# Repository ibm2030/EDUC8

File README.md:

# EDUC8
EDUC-8 recreation by Gwyllym Suter
NOTE: 2024-04-01 PCBs are in the process of being updated and so do not match the latest schematics

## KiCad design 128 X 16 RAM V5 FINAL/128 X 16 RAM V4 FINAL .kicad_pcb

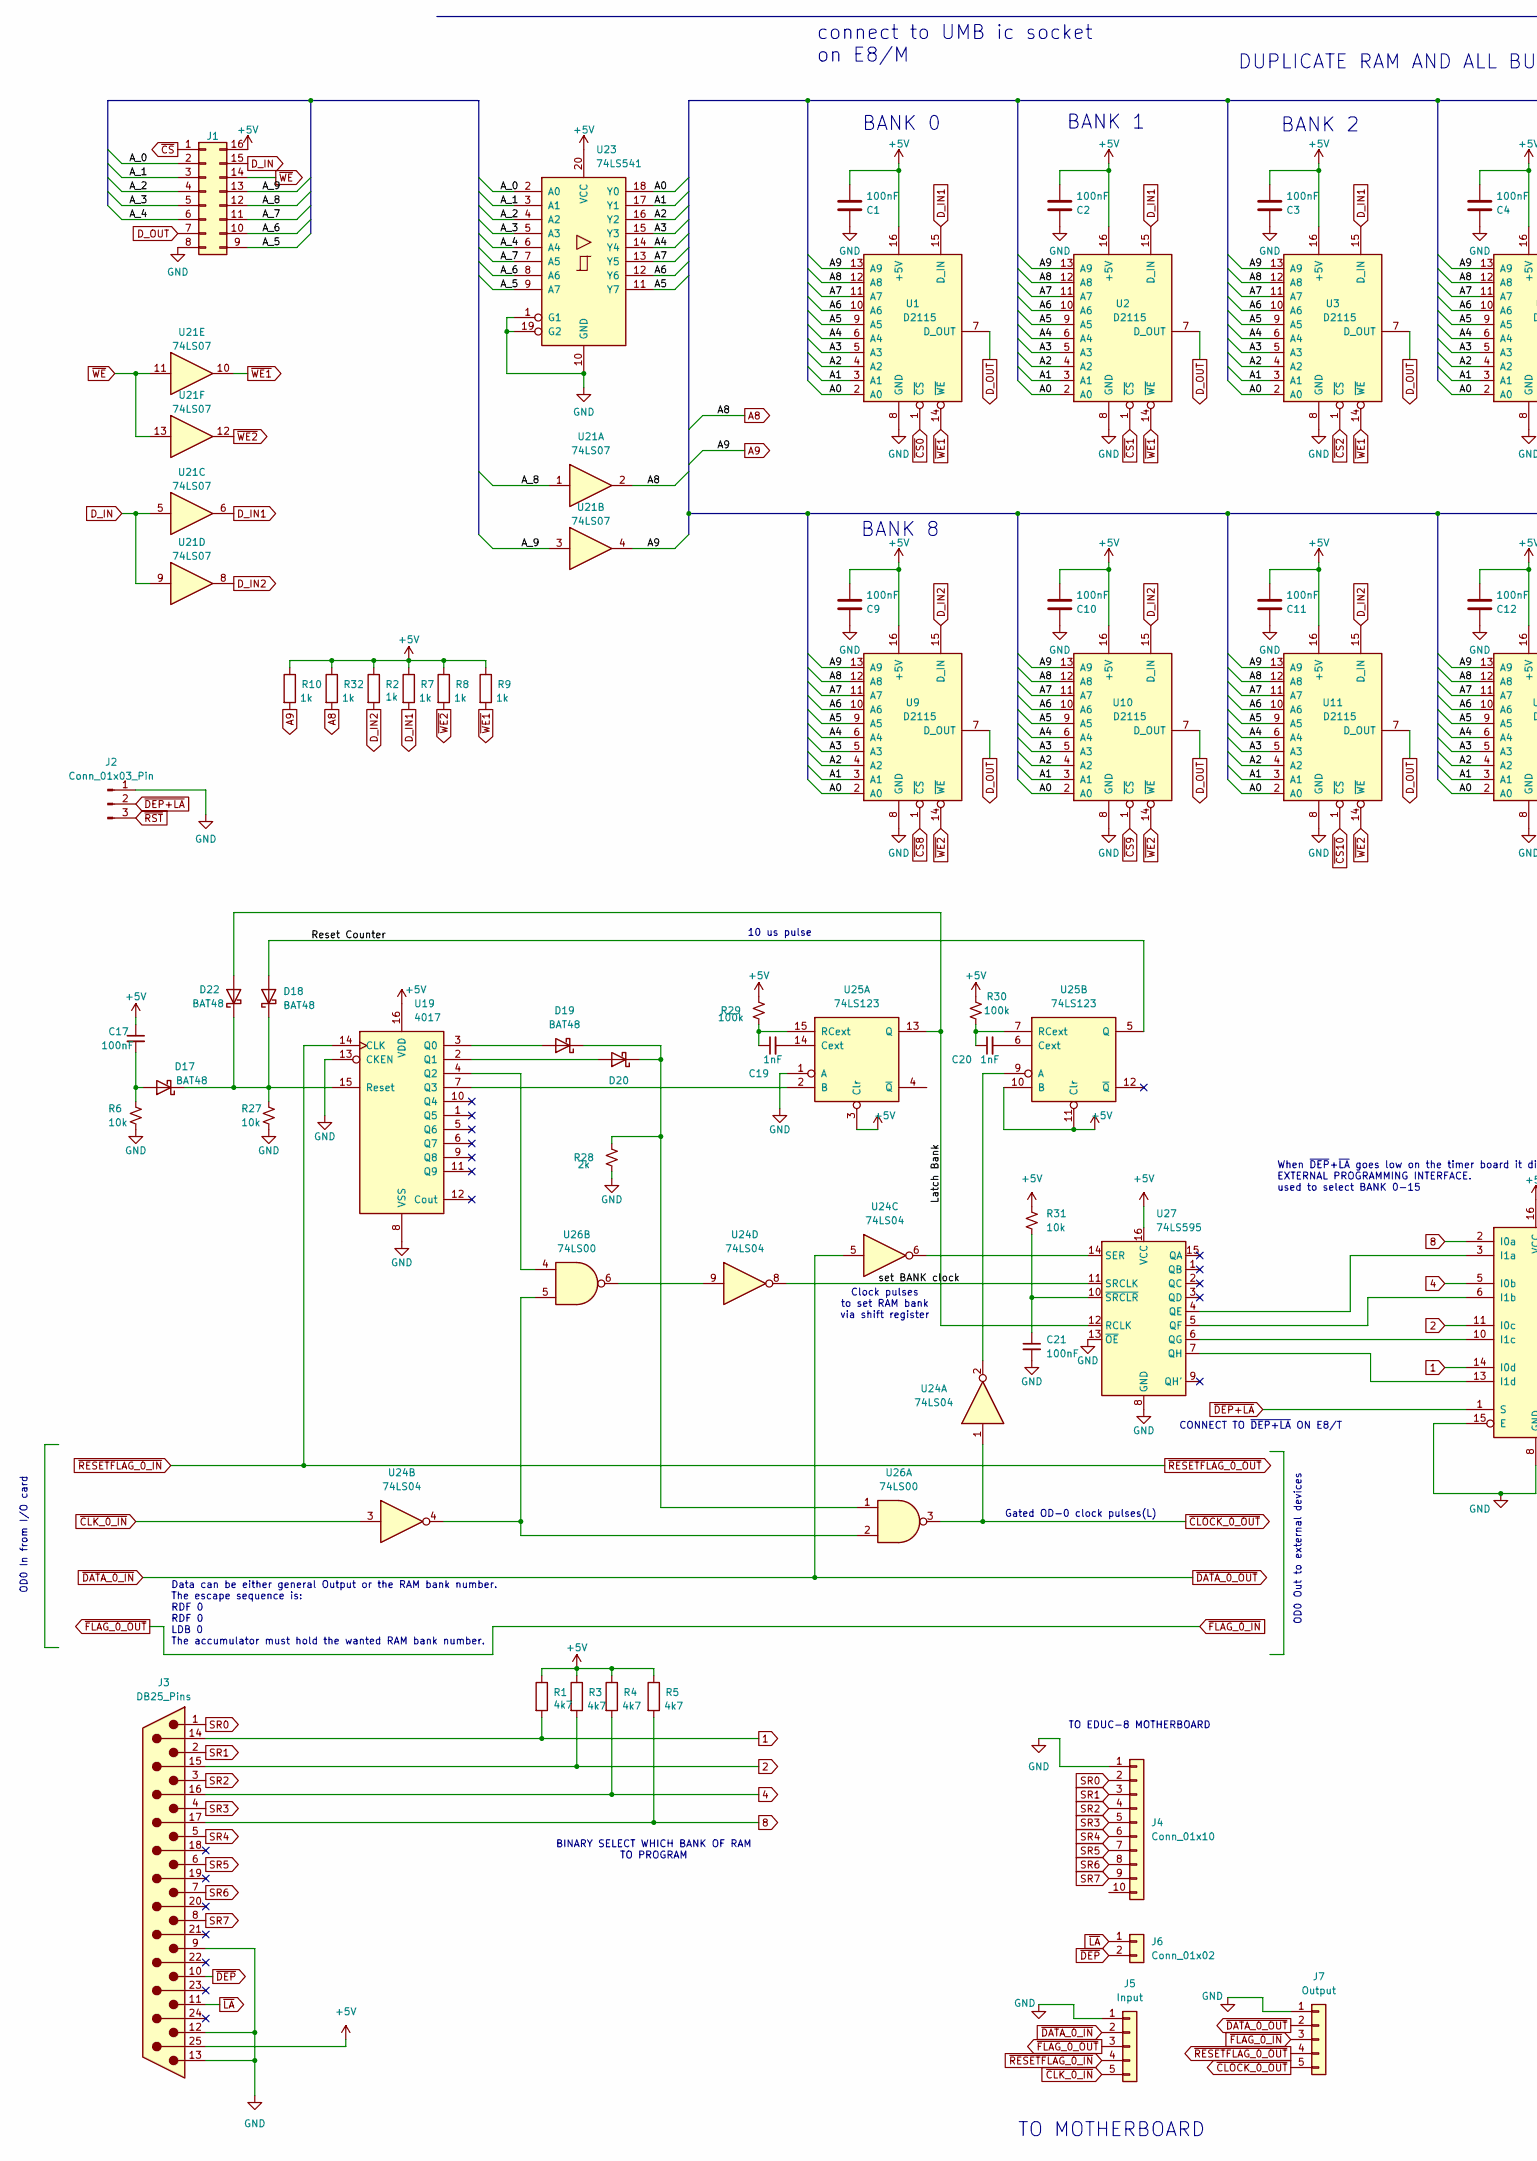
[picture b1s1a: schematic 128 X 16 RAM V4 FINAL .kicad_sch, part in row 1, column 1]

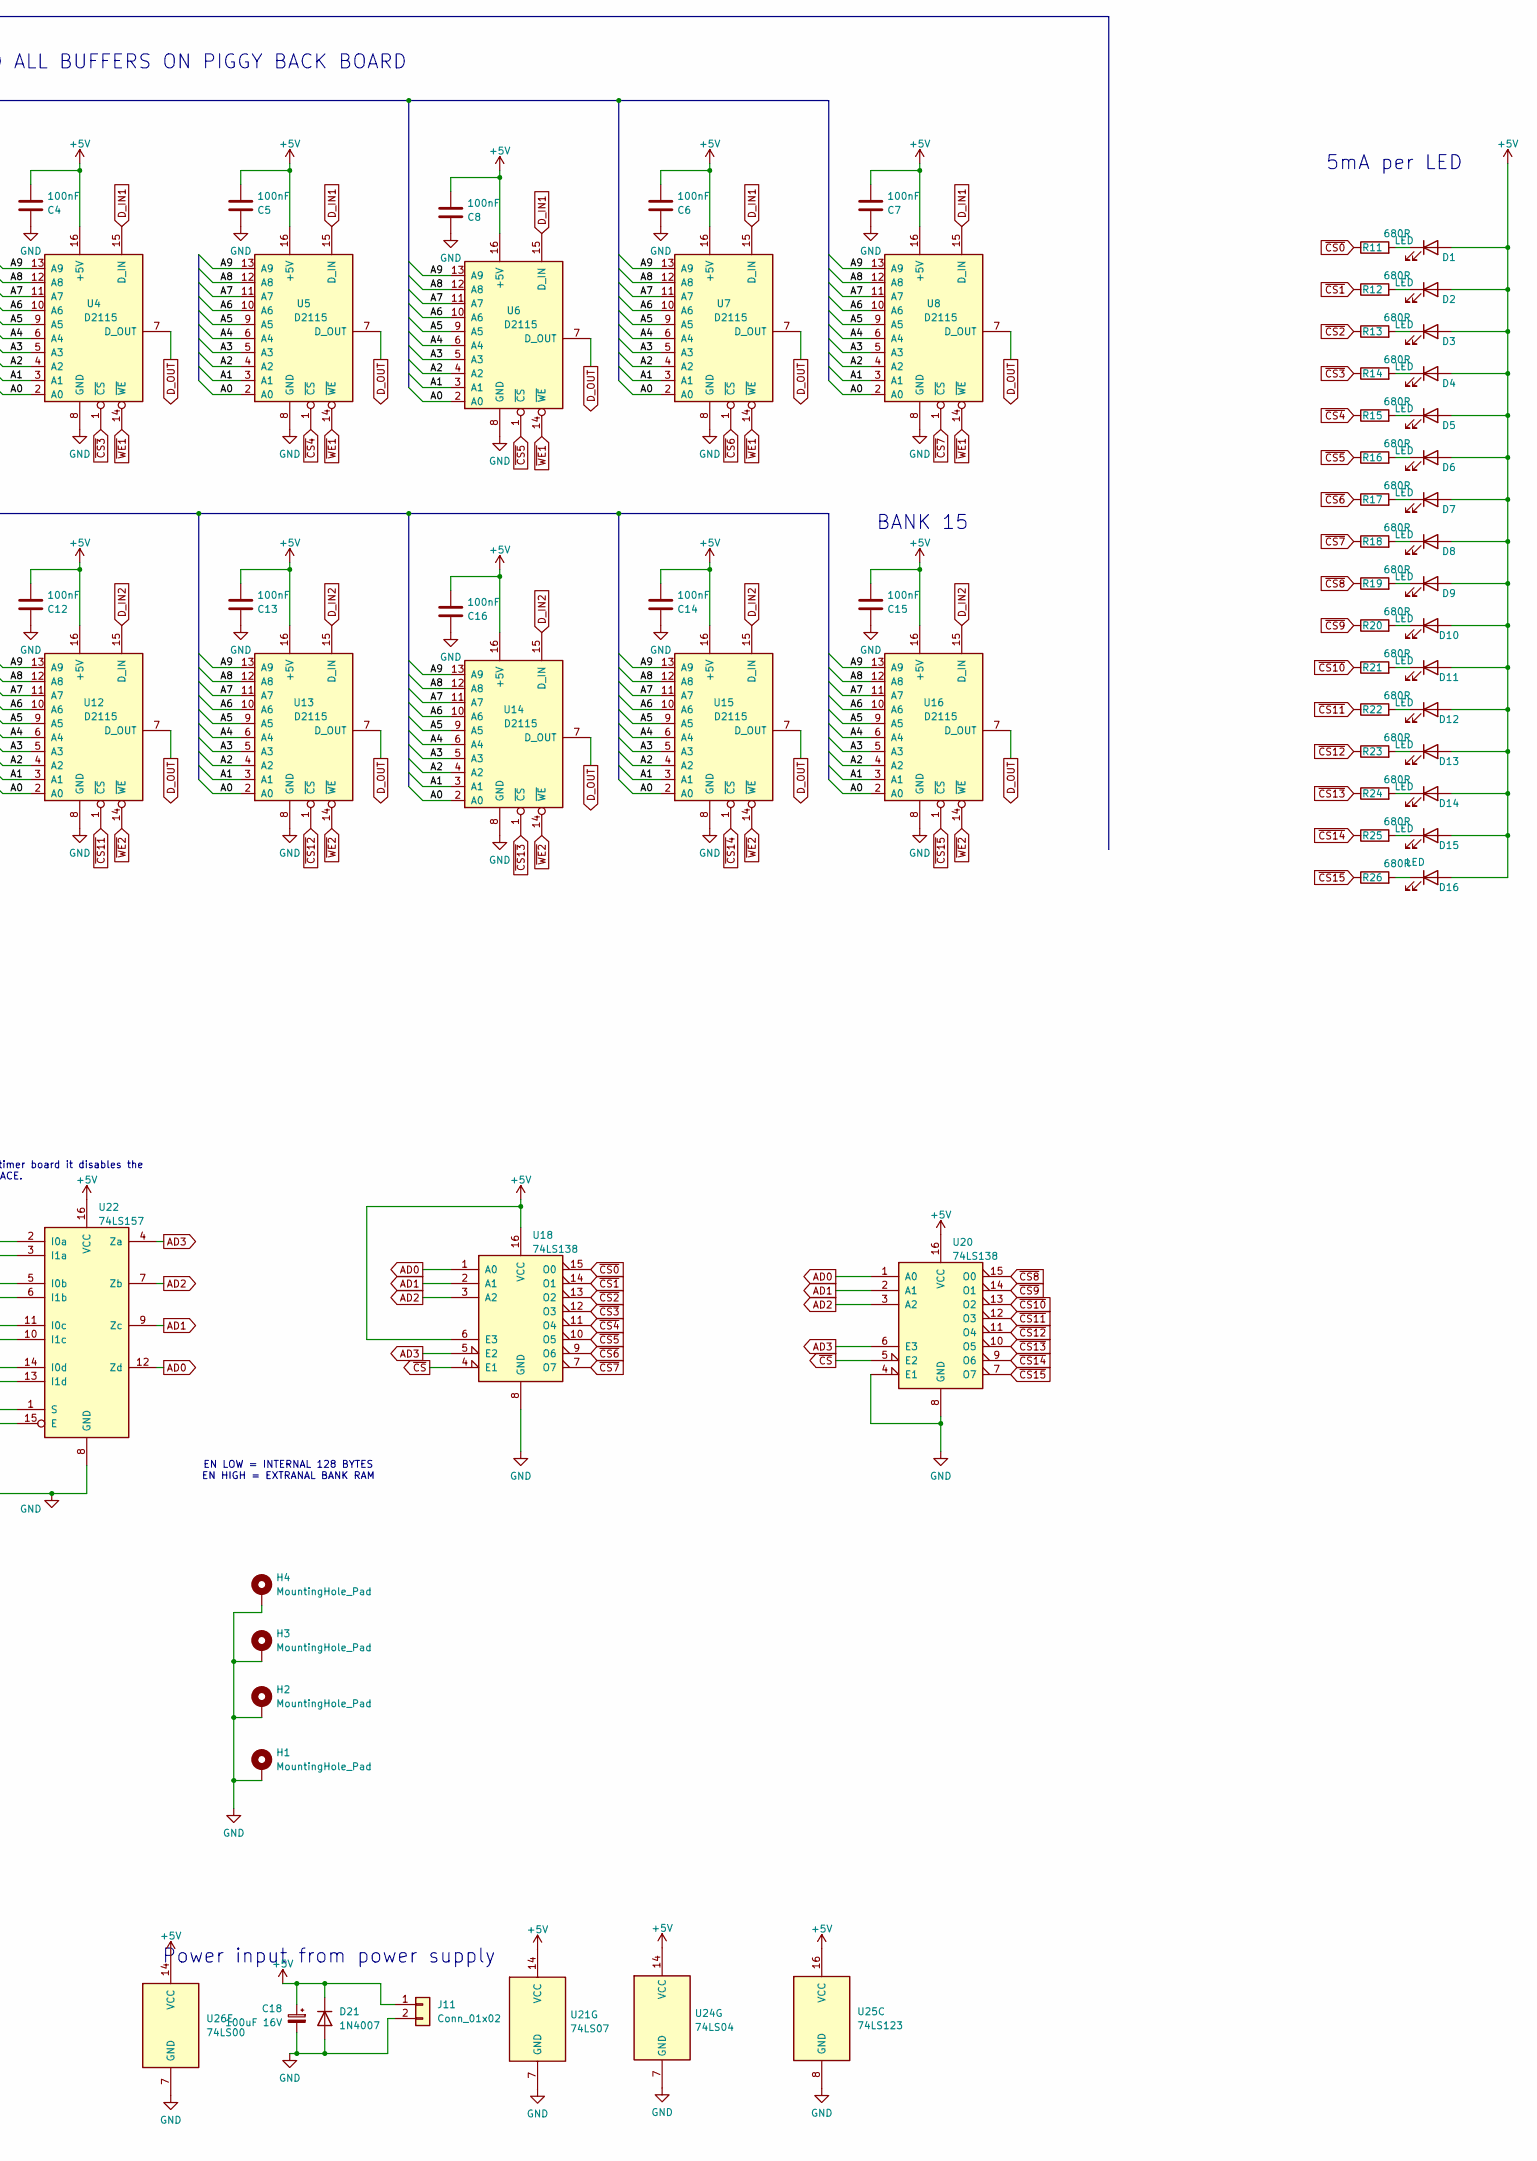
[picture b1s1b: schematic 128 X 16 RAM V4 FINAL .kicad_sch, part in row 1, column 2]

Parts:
C1, C2, C3, C4, C5, C6, C7, C8, C9, C10, C11, C12, C13, C14, C15, C16, C17, C21: 100nF; C_Disc_D4.3mm_W1.9mm_P5.00mm
C18: 100uF 16V; CP_Radial_D12.5mm_P5.00mm
C19, C20: 1nF; C_Disc_D4.3mm_W1.9mm_P5.00mm
D1, D2, D3, D4, D5, D6, D7, D8, D9, D10, D11, D12, D13, D14, D15, D16: LED; LED_D3.0mm
D17, D18, D19, D20, D22: BAT48; D_DO-35_SOD27_P7.62mm_Horizontal
D21: 1N4007; D_DO-41_SOD81_P10.16mm_Horizontal
H1, H2, H3, H4: MountingHole_Pad; MountingHole_3.2mm_M3_DIN965_Pad
J1: Conn_02x08_Counter_Clockwise; DIP-16_W7.62mm_Socket_LongPads
J2: Conn_01x03_Pin; JST_XH_B3B-XH-A_1x03_P2.50mm_Vertical
J3: DB25_Pins; DSUB-25_Pins_Horizontal_P2.77x2.84mm_EdgePinOffset7.70mm_Ho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
J4: Conn_01x10; JST_XH_B10B-XH-A_1x10_P2.50mm_Vertical
J5: Input; JST_XH_B5B-XH-A_1x05_P2.50mm_Vertical
J6: Conn_01x02; JST_XH_B2B-XH-A_1x02_P2.50mm_Vertical
J7: Output; JST_XH_B5B-XH-A_1x05_P2.50mm_Vertical
J11: Conn_01x02; TerminalBlock_Phoenix_MKDS-1,5-2-5.08_1x02_P5.08mm_Horizont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
R1, R3, R4, R5: 4k7; R_Axial_DIN0207_L6.3mm_D2.5mm_P10.16mm_Horizontal
R2, R7, R8, R9, R10, R32: 1k; R_Axial_DIN0207_L6.3mm_D2.5mm_P10.16mm_Horizontal
R6, R27, R31: 10k; R_Axial_DIN0207_L6.3mm_D2.5mm_P10.16mm_Horizontal
R11, R12, R13, R14, R15, R16, R17, R18, R19, R20, R21, R22, R23, R24, R25, R26: 680R; R_Axial_DIN0207_L6.3mm_D2.5mm_P10.16mm_Horizontal
R28: 2k; R_Axial_DIN0207_L6.3mm_D2.5mm_P10.16mm_Horizontal
R29, R30: 100k; R_Axial_DIN0207_L6.3mm_D2.5mm_P10.16mm_Horizontal
U1, U2, U3, U4, U5, U6, U7, U8, U9, U10, U11, U12, U13, U14, U15, U16: D2115; DIP-16_W7.62mm_LongPads
U18, U20: 74LS138; DIP-16_W7.62mm_LongPads
U19: 4017; DIP-16_W7.62mm_LongPads
U21: 74LS07; DIP-14_W7.62mm_LongPads
U22: 74LS157; DIP-16_W7.62mm_LongPads
U23: 74LS541; DIP-20_W7.62mm_LongPads
U24: 74LS04; DIP-14_W7.62mm_LongPads
U25: 74LS123; DIP-16_W7.62mm_LongPads
U26: 74LS00; DIP-14_W7.62mm_LongPads
U27: 74LS595; DIP-16_W7.62mm

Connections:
1: J3.14, R1.2, U22.14 (I0d)
2: J3.15, R3.2, U22.11 (I0c)
4: J3.16, R4.2, U22.5 (I0b)
8: J3.17, R5.2, U22.2 (I0a)
+5V: C1.2, C2.2, C3.2, C4.2, C5.2, C6.2, C7.2, C8.2, C9.2, C10.2, C11.2, C12.2, C13.2, C14.2, C15.2, C16.2, C17.1, C18.1, D1.2 (A), D2.2 (A), D3.2 (A), D4.2 (A), D5.2 (A), D6.2 (A), D7.2 (A), D8.2 (A), D9.2 (A), D10.2 (A), D11.2 (A), D12.2 (A), D13.2 (A), D14.2 (A), D15.2 (A), D16.2 (A), D21.1 (K), J1.16, J3.25, J11.1, R1.1, R2.1, R3.1, R4.1, R5.1, R7.1, R8.1, R9.1, R10.1, R29.1, R30.1, R31.1, R32.1, U1.16 (+5V), U2.16 (+5V), U3.16 (+5V), U4.16 (+5V), U5.16 (+5V), U6.16 (+5V), U7.16 (+5V), U8.16 (+5V), U9.16 (+5V), U10.16 (+5V), U11.16 (+5V), U12.16 (+5V), U13.16 (+5V), U14.16 (+5V), U15.16 (+5V), U16.16 (+5V), U18.6 (E3), U18.16 (VCC), U19.16 (VDD), U20.16 (VCC), U21.14 (VCC), U22.16 (VCC), U23.20 (VCC), U24.14 (VCC), U25.3 (Clr), U25.10 (B), U25.11 (Clr), U25.16 (VCC), U26.14 (VCC), U27.16 (VCC)
/A0: U1.2 (A0), U2.2 (A0), U3.2 (A0), U4.2 (A0), U5.2 (A0), U6.2 (A0), U7.2 (A0), U8.2 (A0), U9.2 (A0), U10.2 (A0), U11.2 (A0), U12.2 (A0), U13.2 (A0), U14.2 (A0), U15.2 (A0), U16.2 (A0), U23.18 (Y0)
/A1: U1.3 (A1), U2.3 (A1), U3.3 (A1), U4.3 (A1), U5.3 (A1), U6.3 (A1), U7.3 (A1), U8.3 (A1), U9.3 (A1), U10.3 (A1), U11.3 (A1), U12.3 (A1), U13.3 (A1), U14.3 (A1), U15.3 (A1), U16.3 (A1), U23.17 (Y1)
/A2: U1.4 (A2), U2.4 (A2), U3.4 (A2), U4.4 (A2), U5.4 (A2), U6.4 (A2), U7.4 (A2), U8.4 (A2), U9.4 (A2), U10.4 (A2), U11.4 (A2), U12.4 (A2), U13.4 (A2), U14.4 (A2), U15.4 (A2), U16.4 (A2), U23.16 (Y2)
/A3: U1.5 (A3), U2.5 (A3), U3.5 (A3), U4.5 (A3), U5.5 (A3), U6.5 (A3), U7.5 (A3), U8.5 (A3), U9.5 (A3), U10.5 (A3), U11.5 (A3), U12.5 (A3), U13.5 (A3), U14.5 (A3), U15.5 (A3), U16.5 (A3), U23.15 (Y3)
/A4: U1.6 (A4), U2.6 (A4), U3.6 (A4), U4.6 (A4), U5.6 (A4), U6.6 (A4), U7.6 (A4), U8.6 (A4), U9.6 (A4), U10.6 (A4), U11.6 (A4), U12.6 (A4), U13.6 (A4), U14.6 (A4), U15.6 (A4), U16.6 (A4), U23.14 (Y4)
/A5: U1.9 (A5), U2.9 (A5), U3.9 (A5), U4.9 (A5), U5.9 (A5), U6.9 (A5), U7.9 (A5), U8.9 (A5), U9.9 (A5), U10.9 (A5), U11.9 (A5), U12.9 (A5), U13.9 (A5), U14.9 (A5), U15.9 (A5), U16.9 (A5), U23.11 (Y7)
/A6: U1.10 (A6), U2.10 (A6), U3.10 (A6), U4.10 (A6), U5.10 (A6), U6.10 (A6), U7.10 (A6), U8.10 (A6), U9.10 (A6), U10.10 (A6), U11.10 (A6), U12.10 (A6), U13.10 (A6), U14.10 (A6), U15.10 (A6), U16.10 (A6), U23.12 (Y6)
/A7: U1.11 (A7), U2.11 (A7), U3.11 (A7), U4.11 (A7), U5.11 (A7), U6.11 (A7), U7.11 (A7), U8.11 (A7), U9.11 (A7), U10.11 (A7), U11.11 (A7), U12.11 (A7), U13.11 (A7), U14.11 (A7), U15.11 (A7), U16.11 (A7), U23.13 (Y5)
/A_0: J1.2, U23.2 (A0)
/A_1: J1.3, U23.3 (A1)
/A_2: J1.4, U23.4 (A2)
/A_3: J1.5, U23.5 (A3)
/A_4: J1.6, U23.6 (A4)
/A_5: J1.9, U23.9 (A7)
/A_6: J1.10, U23.8 (A6)
/A_7: J1.11, U23.7 (A5)
/A_8: J1.12, U21.1
/A_9: J1.13, U21.3
/Latch Bank: D22.2 (A), U25.13 (Q), U27.12 (RCLK)
/Reset Counter: D18.2 (A), U25.5 (Q)
/set BANK clock: U24.8, U27.11 (SRCLK)
A8: R32.2, U1.12 (A8), U2.12 (A8), U3.12 (A8), U4.12 (A8), U5.12 (A8), U6.12 (A8), U7.12 (A8), U8.12 (A8), U9.12 (A8), U10.12 (A8), U11.12 (A8), U12.12 (A8), U13.12 (A8), U14.12 (A8), U15.12 (A8), U16.12 (A8), U21.2
A9: R10.2, U1.13 (A9), U2.13 (A9), U3.13 (A9), U4.13 (A9), U5.13 (A9), U6.13 (A9), U7.13 (A9), U8.13 (A9), U9.13 (A9), U10.13 (A9), U11.13 (A9), U12.13 (A9), U13.13 (A9), U14.13 (A9), U15.13 (A9), U16.13 (A9), U21.4
AD0: U18.1 (A0), U20.1 (A0), U22.12 (Zd)
AD1: U18.2 (A1), U20.2 (A1), U22.9 (Zc)
AD2: U18.3 (A2), U20.3 (A2), U22.7 (Zb)
AD3: U18.5 (E2), U20.6 (E3), U22.4 (Za)
D_IN: J1.15, U21.5, U21.9
D_IN1: R7.2, U1.15 (D_IN), U2.15 (D_IN), U3.15 (D_IN), U4.15 (D_IN), U5.15 (D_IN), U6.15 (D_IN), U7.15 (D_IN), U8.15 (D_IN), U21.6
D_IN2: R2.2, U9.15 (D_IN), U10.15 (D_IN), U11.15 (D_IN), U12.15 (D_IN), U13.15 (D_IN), U14.15 (D_IN), U15.15 (D_IN), U16.15 (D_IN), U21.8
D_OUT: J1.7, U1.7 (D_OUT), U2.7 (D_OUT), U3.7 (D_OUT), U4.7 (D_OUT), U5.7 (D_OUT), U6.7 (D_OUT), U7.7 (D_OUT), U8.7 (D_OUT), U9.7 (D_OUT), U10.7 (D_OUT), U11.7 (D_OUT), U12.7 (D_OUT), U13.7 (D_OUT), U14.7 (D_OUT), U15.7 (D_OUT), U16.7 (D_OUT)
GND: C1.1, C2.1, C3.1, C4.1, C5.1, C6.1, C7.1, C8.1, C9.1, C10.1, C11.1, C12.1, C13.1, C14.1, C15.1, C16.1, C18.2, C21.2, D21.2 (A), H1.1, H2.1, H3.1, H4.1, J1.8, J2.1, J3.9, J3.12, J3.13, J4.1, J5.1, J7.1, J11.2, R6.2, R27.2, R28.2, U1.8 (GND), U2.8 (GND), U3.8 (GND), U4.8 (GND), U5.8 (GND), U6.8 (GND), U7.8 (GND), U8.8 (GND), U9.8 (GND), U10.8 (GND), U11.8 (GND), U12.8 (GND), U13.8 (GND), U14.8 (GND), U15.8 (GND), U16.8 (GND), U18.8 (GND), U19.8 (VSS), U19.13 (CKEN), U20.4 (E1), U20.8 (GND), U21.7 (GND), U22.8 (GND), U22.15 (E), U23.1 (G1), U23.10 (GND), U23.19 (G2), U24.7 (GND), U25.1 (A), U25.8 (GND), U26.7 (GND), U27.8 (GND), U27.13 (~OE)
unnamed: D1.1 (K), R11.2
unnamed: D2.1 (K), R12.2
unnamed: D3.1 (K), R13.2
unnamed: D4.1 (K), R14.2
unnamed: D5.1 (K), R15.2
unnamed: D6.1 (K), R16.2
unnamed: D7.1 (K), R17.2
unnamed: D8.1 (K), R18.2
unnamed: D9.1 (K), R19.2
unnamed: D10.1 (K), R20.2
unnamed: D11.1 (K), R21.2
unnamed: D12.1 (K), R22.2
unnamed: D13.1 (K), R23.2
unnamed: D14.1 (K), R24.2
unnamed: D15.1 (K), R25.2
unnamed: D16.1 (K), R26.2
unnamed: C17.2, D17.2 (A), R6.1
unnamed: D17.1 (K), D18.1 (K), D22.1 (K), R27.1, U19.15 (Reset)
unnamed: D19.2 (A), U19.3 (Q0)
unnamed: D19.1 (K), D20.1 (K), R28.1, U26.1
unnamed: D20.2 (A), U19.2 (Q1)
unnamed: U19.4 (Q2), U26.4
unnamed: U19.7 (Q3), U25.2 (B)
unnamed: U22.3 (I1a), U27.4 (QE)
unnamed: U22.6 (I1b), U27.5 (QF)
unnamed: U22.10 (I1c), U27.6 (QG)
unnamed: U22.13 (I1d), U27.7 (QH)
unnamed: U24.4, U26.2, U26.5
unnamed: U24.9, U26.6
unnamed: C19.2, U25.14 (Cext)
unnamed: C19.1, R29.2, U25.15 (RCext)
unnamed: U24.2, U25.9 (A)
unnamed: C20.2, U25.6 (Cext)
unnamed: C20.1, R30.2, U25.7 (RCext)
unnamed: U24.6, U27.14 (SER)
unnamed: C21.1, R31.2, U27.10 (~SRCLR)
SR0: J3.1, J4.2
SR1: J3.2, J4.3
SR2: J3.3, J4.4
SR3: J3.4, J4.5
SR4: J3.5, J4.6
SR5: J3.6, J4.7
SR6: J3.7, J4.8
SR7: J3.8, J4.9
~CLK_0_IN: J5.5, U24.3
~CLOCK_0_OUT: J7.5, U24.1, U26.3
~CS0: R11.1, U1.1 (~CS), U18.15 (O0)
~CS1: R12.1, U2.1 (~CS), U18.14 (O1)
~CS2: R13.1, U3.1 (~CS), U18.13 (O2)
~CS3: R14.1, U4.1 (~CS), U18.12 (O3)
~CS4: R15.1, U5.1 (~CS), U18.11 (O4)
~CS5: R16.1, U6.1 (~CS), U18.10 (O5)
~CS6: R17.1, U7.1 (~CS), U18.9 (O6)
~CS7: R18.1, U8.1 (~CS), U18.7 (O7)
~CS8: R19.1, U9.1 (~CS), U20.15 (O0)
~CS9: R20.1, U10.1 (~CS), U20.14 (O1)
~CS10: R21.1, U11.1 (~CS), U20.13 (O2)
~CS11: R22.1, U12.1 (~CS), U20.12 (O3)
~CS12: R23.1, U13.1 (~CS), U20.11 (O4)
~CS13: R24.1, U14.1 (~CS), U20.10 (O5)
~CS14: R25.1, U15.1 (~CS), U20.9 (O6)
~CS15: R26.1, U16.1 (~CS), U20.7 (O7)
~CS: J1.1, U18.4 (E1), U20.5 (E2)
~DATA_0_IN: J5.2, J7.2, U24.5
~DEP+LA: J2.2, U22.1 (S)
~DEP: J3.10, J6.2
~FLAG_0_IN: J5.3, J7.3
~LA: J3.11, J6.1
~RESETFLAG_0_IN: J5.4, J7.4, U19.14 (CLK)
~RST: J2.3
~WE1: R9.2, U1.14 (~WE), U2.14 (~WE), U3.14 (~WE), U4.14 (~WE), U5.14 (~WE), U6.14 (~WE), U7.14 (~WE), U8.14 (~WE), U21.10
~WE2: R8.2, U9.14 (~WE), U10.14 (~WE), U11.14 (~WE), U12.14 (~WE), U13.14 (~WE), U14.14 (~WE), U15.14 (~WE), U16.14 (~WE), U21.12
~WE: J1.14, U21.11, U21.13

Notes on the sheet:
connect to UMB ic socket on E8/M
10 us pulse
BANK 15
EN LOW = INTERNAL 128 BYTES EN HIGH = EXTRANAL BANK RAM
BANK 0
DUPLICATE RAM AND ALL BUFFERS ON PIGGY BACK BOARD
Gated OD-0 clock pulses(L)
TO EDUC-8 MOTHERBOARD
OD0 Out to external devices
When ~{DEP}+~{LA} goes low on the timer board it disables the EXTERNAL PROGRAMMING INTERFACE. used to select BANK 0-15
OD0 In from I/O card
Clock pulses to set RAM bank via shift register
Power input from power supply
BANK 8
5mA per LED
Data can be either general Output or the RAM bank number. The escape sequence is: RDF 0 RDF 0 LDB 0 The accumulator must hold the wanted RAM bank number.
BANK 1
BANK 2
CONNECT TO ~{DEP+LA} ON E8/T
TO MOTHERBOARD
BINARY SELECT WHICH BANK OF RAM TO PROGRAM

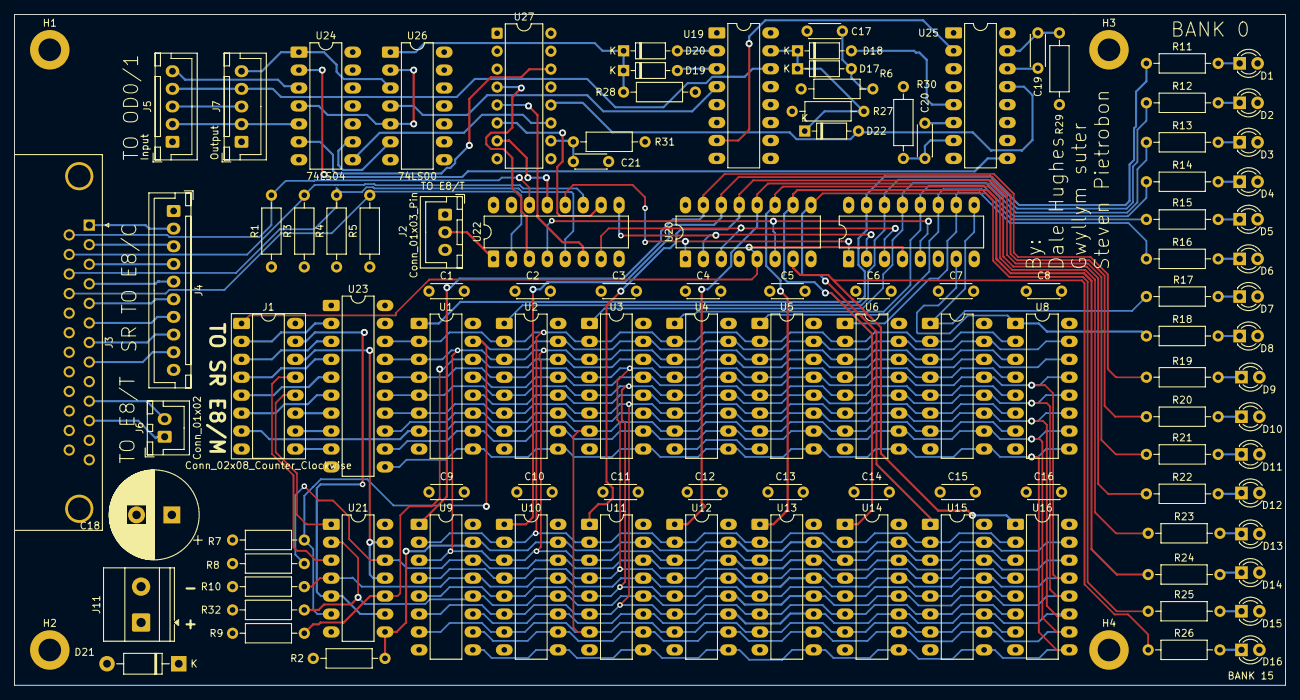
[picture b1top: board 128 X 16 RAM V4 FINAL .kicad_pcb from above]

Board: 4 copper layers, 180.0 x 95.0 mm, 113 parts (0 on the bottom side), 109 nets.

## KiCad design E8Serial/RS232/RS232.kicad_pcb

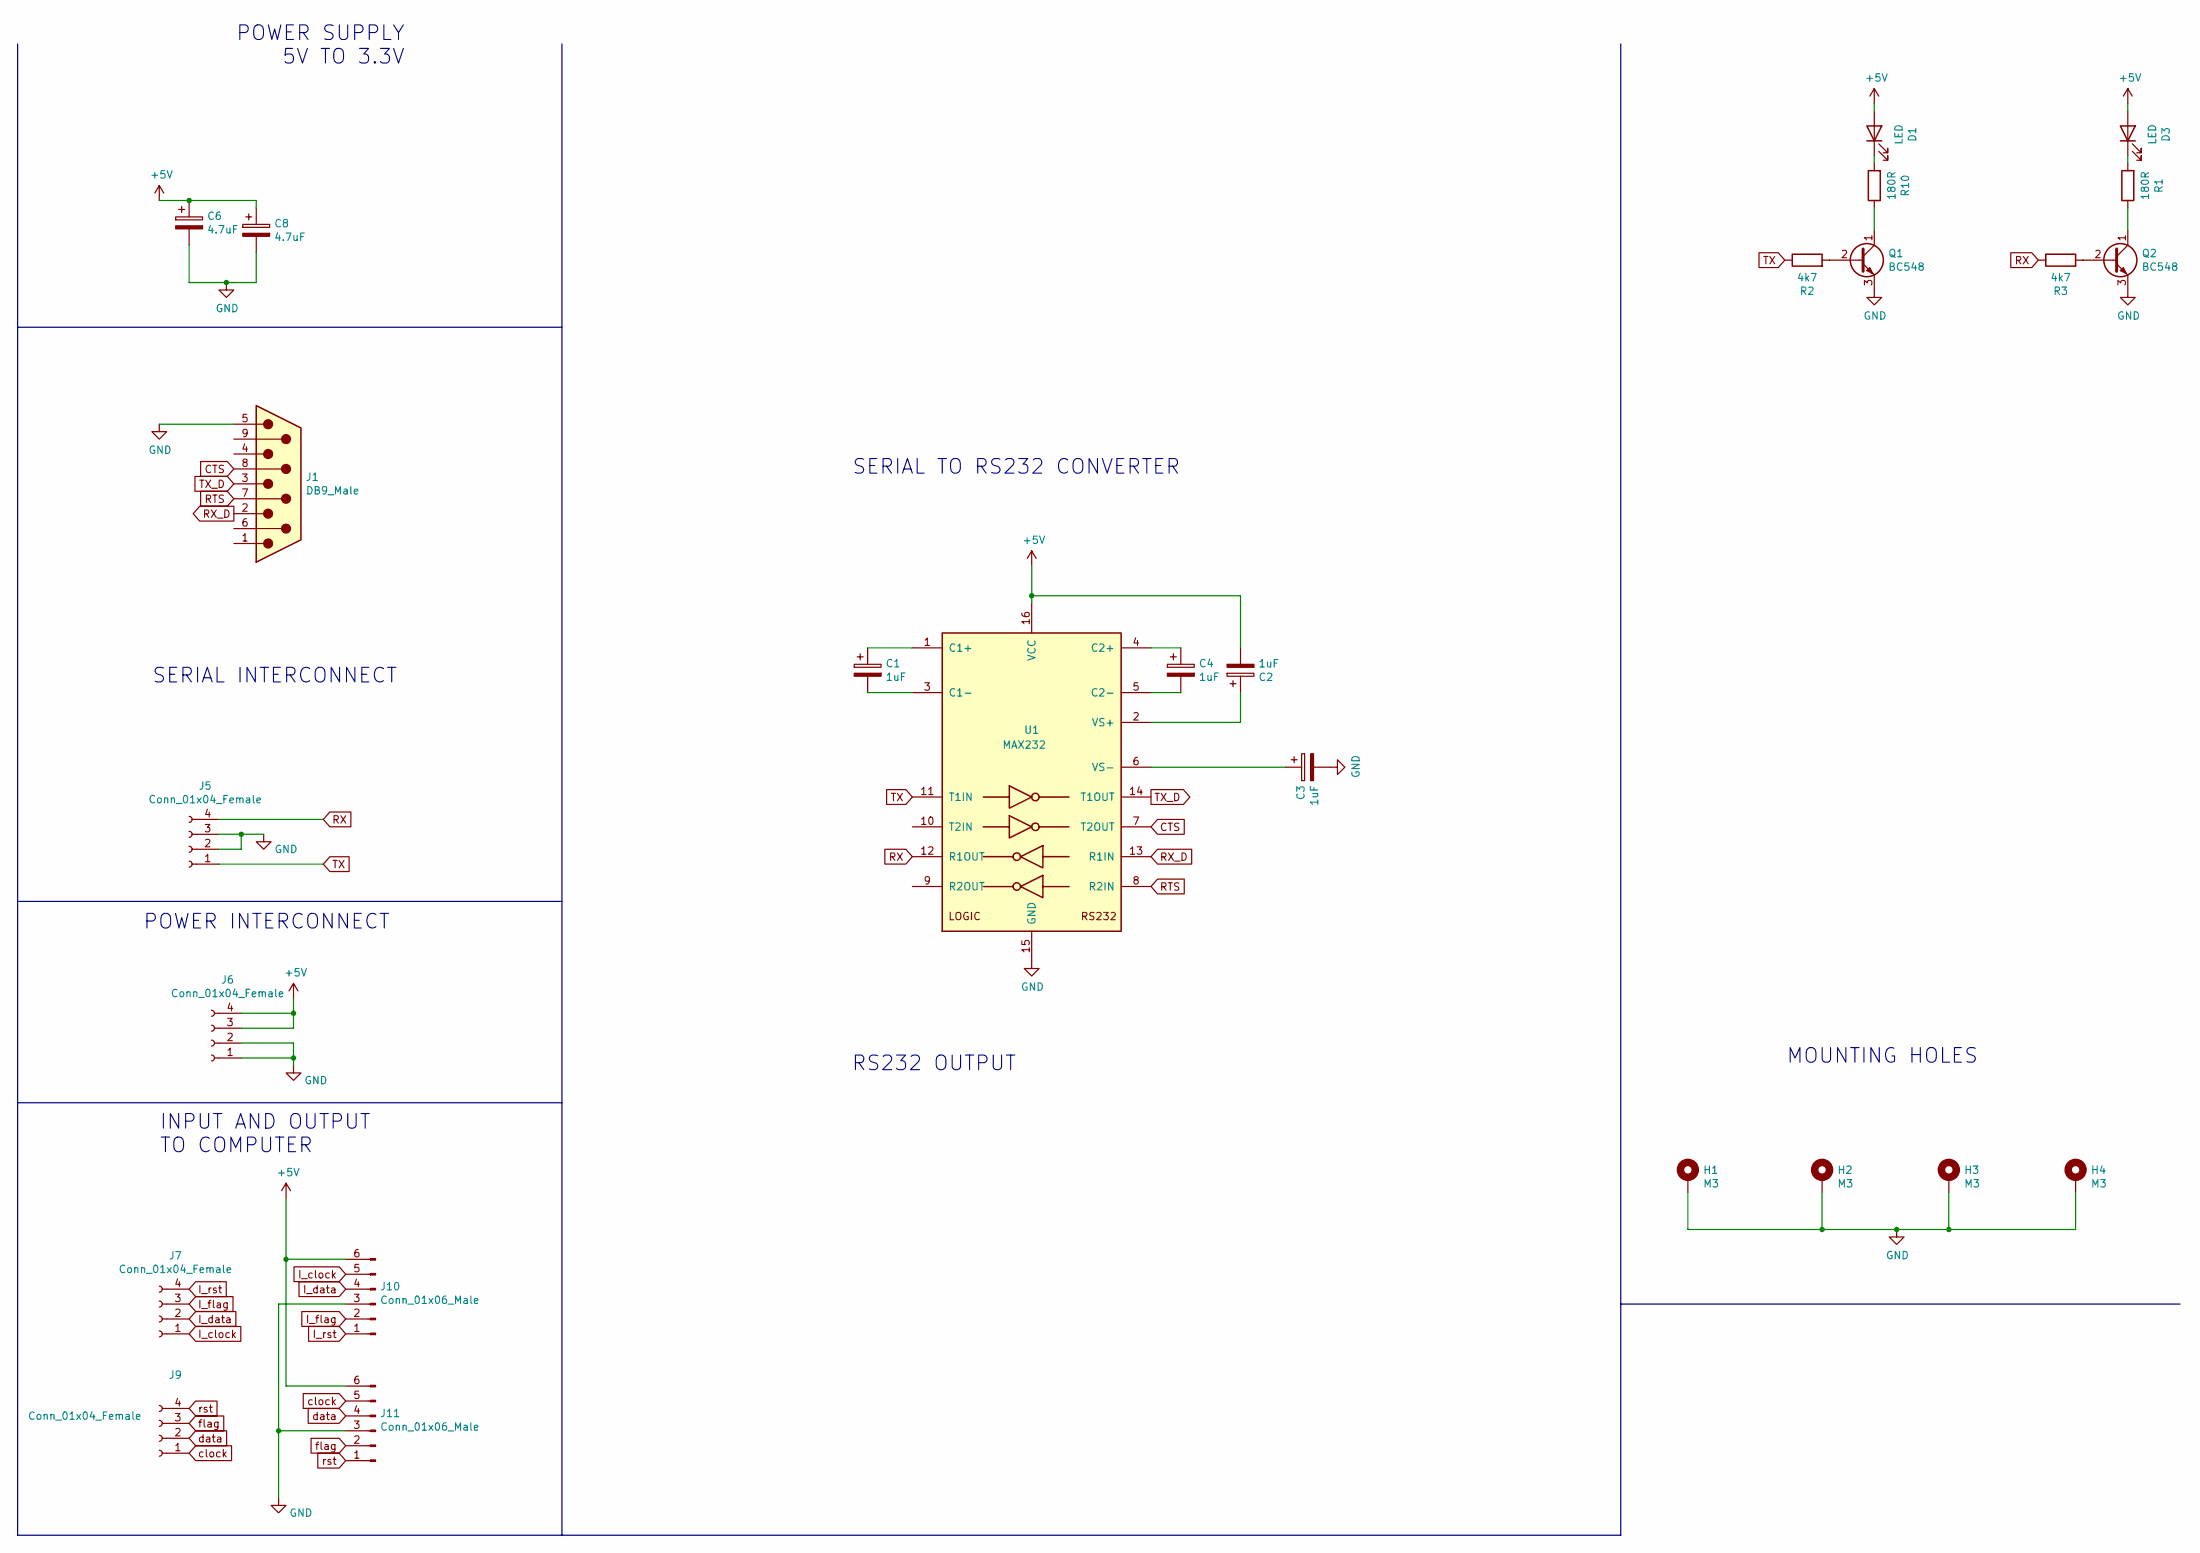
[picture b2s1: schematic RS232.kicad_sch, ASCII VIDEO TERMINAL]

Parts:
C1, C2, C3, C4: 1uF; CP_Radial_D5.0mm_P2.50mm
C6, C8: 4.7uF; CP_Axial_L11.0mm_D6.0mm_P18.00mm_Horizontal
D1, D3: LED; LED_D5.0mm_Horizontal_O1.27mm_Z3.0mm
H1, H2, H3, H4: M3; MountingHole_3.2mm_M3_Pad_Via
J1: DB9_Male; DSUB-9_Male_Horizontal_P2.77x2.84mm_EdgePinOffset4.94mm_Hou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
J5, J6, J7, J9: Conn_01x04_Female; PinSocket_1x04_P2.54mm_Vertical
J10, J11: Conn_01x06_Male; Molex_KK-254_AE-6410-06A_1x06_P2.54mm_Vertical
Q1, Q2: BC548; TO-92_Inline_Wide
R1, R10: 180R; R_Axial_DIN0207_L6.3mm_D2.5mm_P10.16mm_Horizontal
R2, R3: 4k7; R_Axial_DIN0207_L6.3mm_D2.5mm_P10.16mm_Horizontal
U1: MAX232; DIP-16_W7.62mm

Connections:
+5V: C2.2, C6.1, C8.1, D1.2 (A), D3.2 (A), J6.3, J6.4, J10.6, J11.6, U1.16 (VCC)
CTS: J1.8, U1.7 (T2OUT)
GND: C3.2, C6.2, C8.2, H1.1, H2.1, H3.1, H4.1, J1.5, J5.2, J5.3, J6.1, J6.2, J10.3, J11.3, Q1.3 (E), Q2.3 (E), U1.15 (GND)
I_clock: J7.1, J10.5
I_data: J7.2, J10.4
I_flag: J7.3, J10.2
I_rst: J7.4, J10.1
unnamed: C1.1, U1.1 (C1+)
unnamed: C1.2, U1.3 (C1-)
unnamed: C2.1, U1.2 (VS+)
unnamed: C3.1, U1.6 (VS-)
unnamed: C4.1, U1.4 (C2+)
unnamed: C4.2, U1.5 (C2-)
unnamed: D1.1 (K), R10.2
unnamed: D3.1 (K), R1.2
unnamed: Q1.1 (C), R10.1
unnamed: Q1.2 (B), R2.2
unnamed: Q2.1 (C), R1.1
unnamed: Q2.2 (B), R3.2
RTS: J1.7, U1.8 (R2IN)
RX: J5.4, R3.1, U1.12 (R1OUT)
RX_D: J1.2, U1.13 (R1IN)
TX: J5.1, R2.1, U1.11 (T1IN)
TX_D: J1.3, U1.14 (T1OUT)
clock: J9.1, J11.5
data: J9.2, J11.4
flag: J9.3, J11.2
rst: J9.4, J11.1

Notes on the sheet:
SERIAL INTERCONNECT
POWER INTERCONNECT
MOUNTING HOLES
SERIAL TO RS232 CONVERTER
POWER SUPPLY 5V TO 3.3V
RS232 OUTPUT
INPUT AND OUTPUT TO COMPUTER

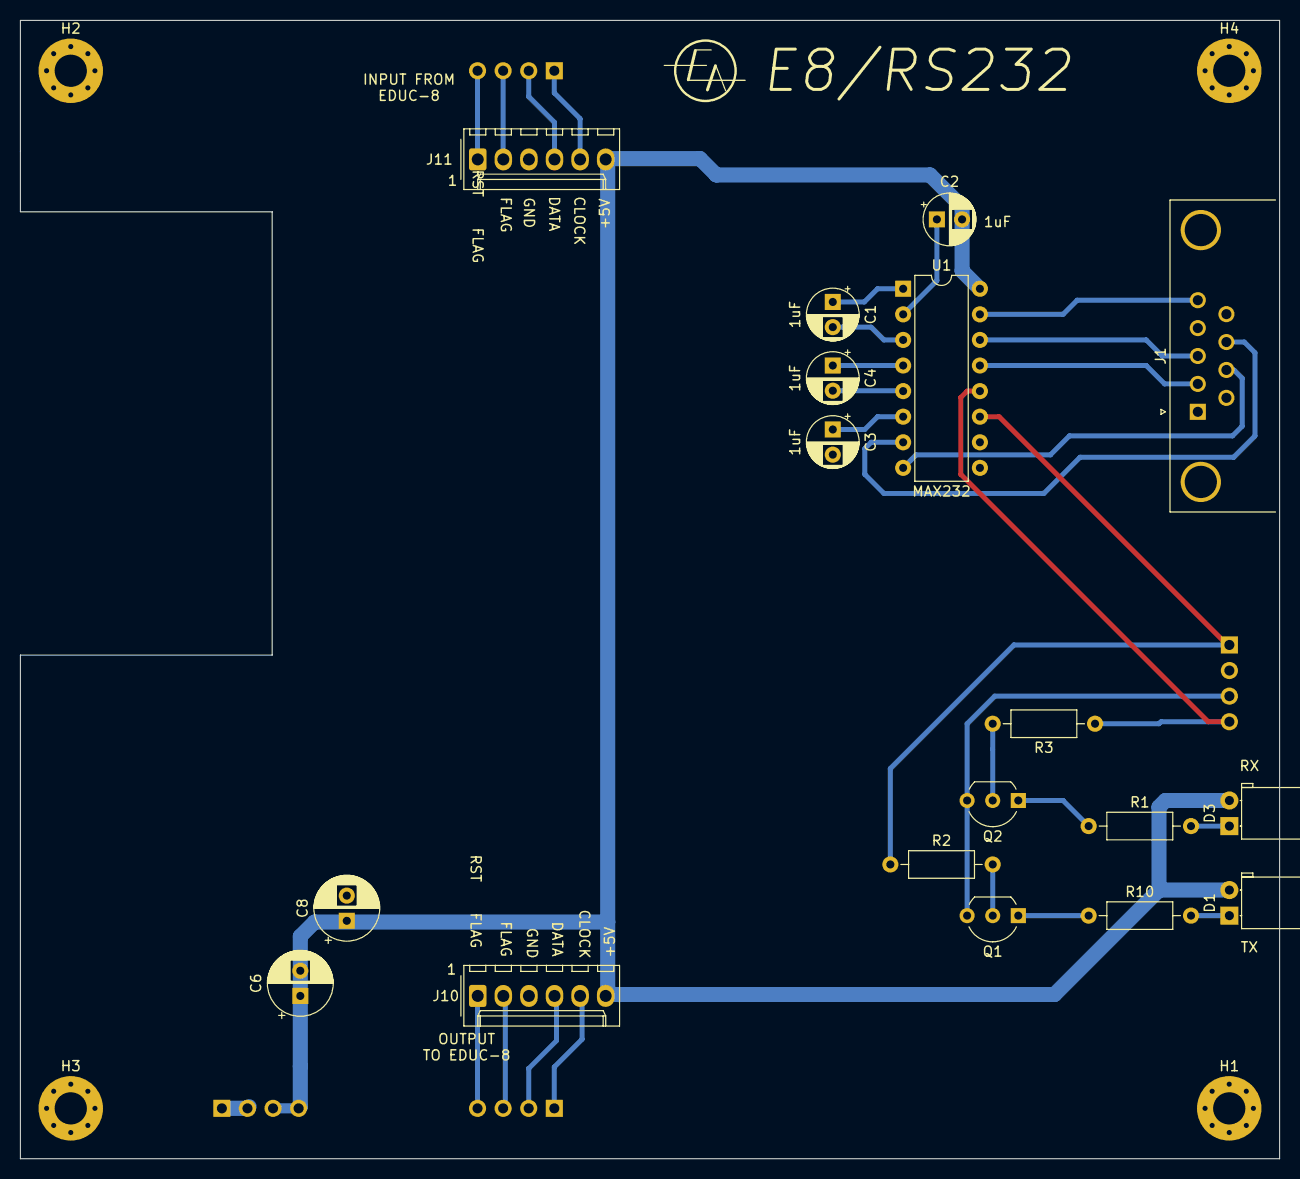
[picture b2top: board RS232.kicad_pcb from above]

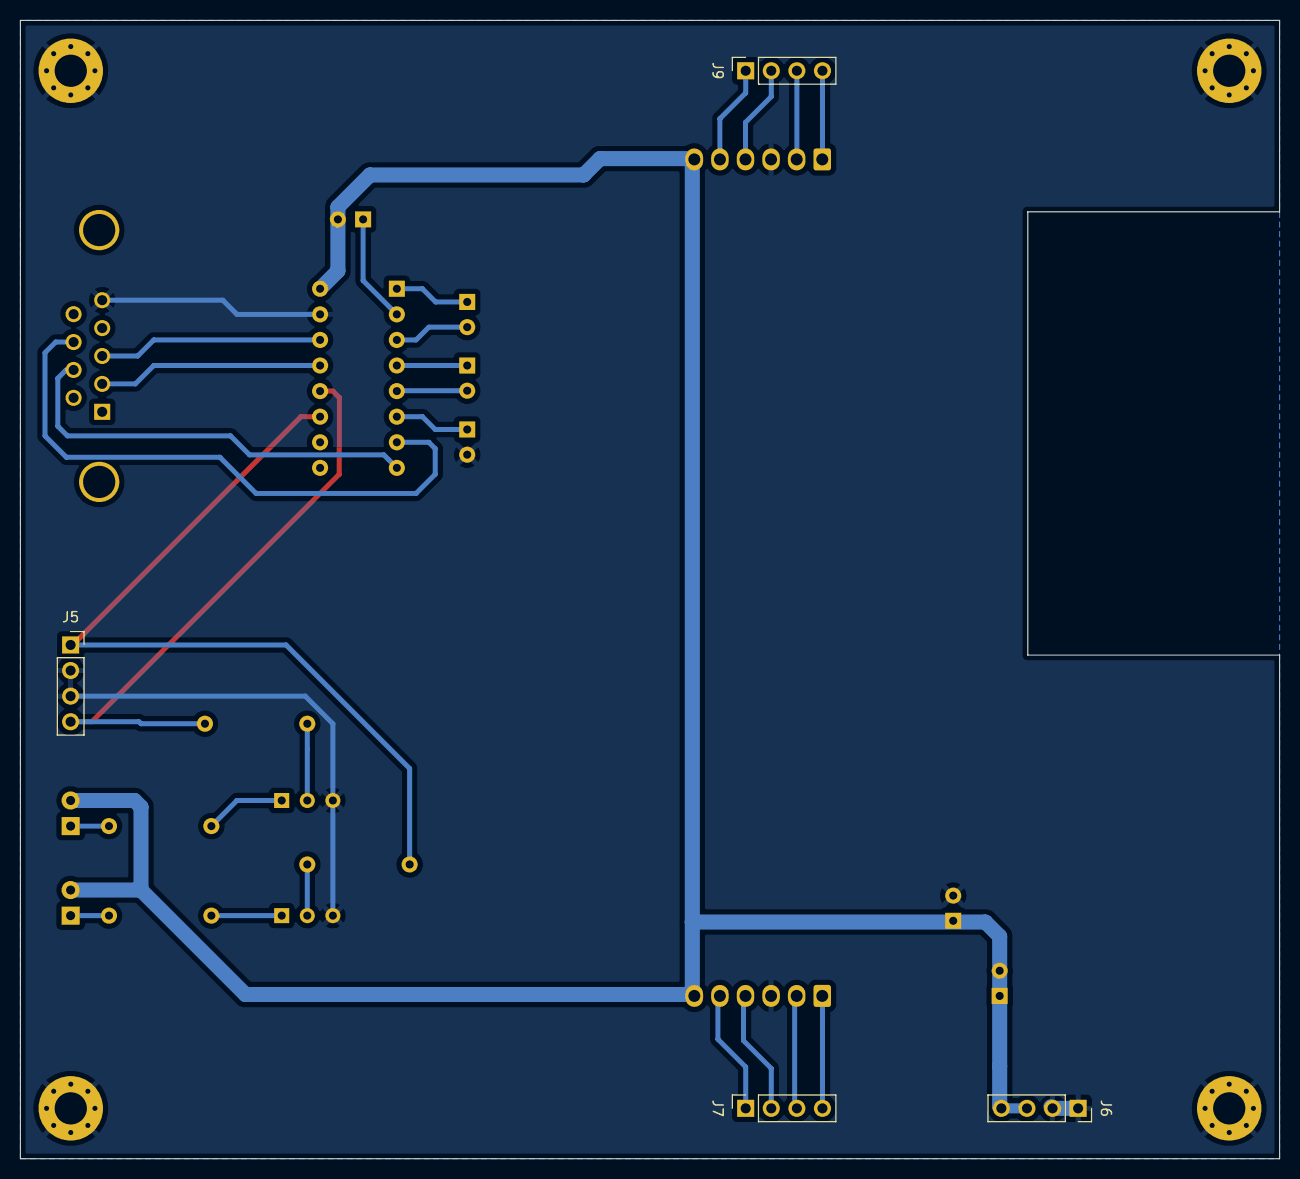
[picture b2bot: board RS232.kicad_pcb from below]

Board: 2 copper layers, 125.0 x 113.0 mm, 26 parts (4 on the bottom side), 28 nets.
